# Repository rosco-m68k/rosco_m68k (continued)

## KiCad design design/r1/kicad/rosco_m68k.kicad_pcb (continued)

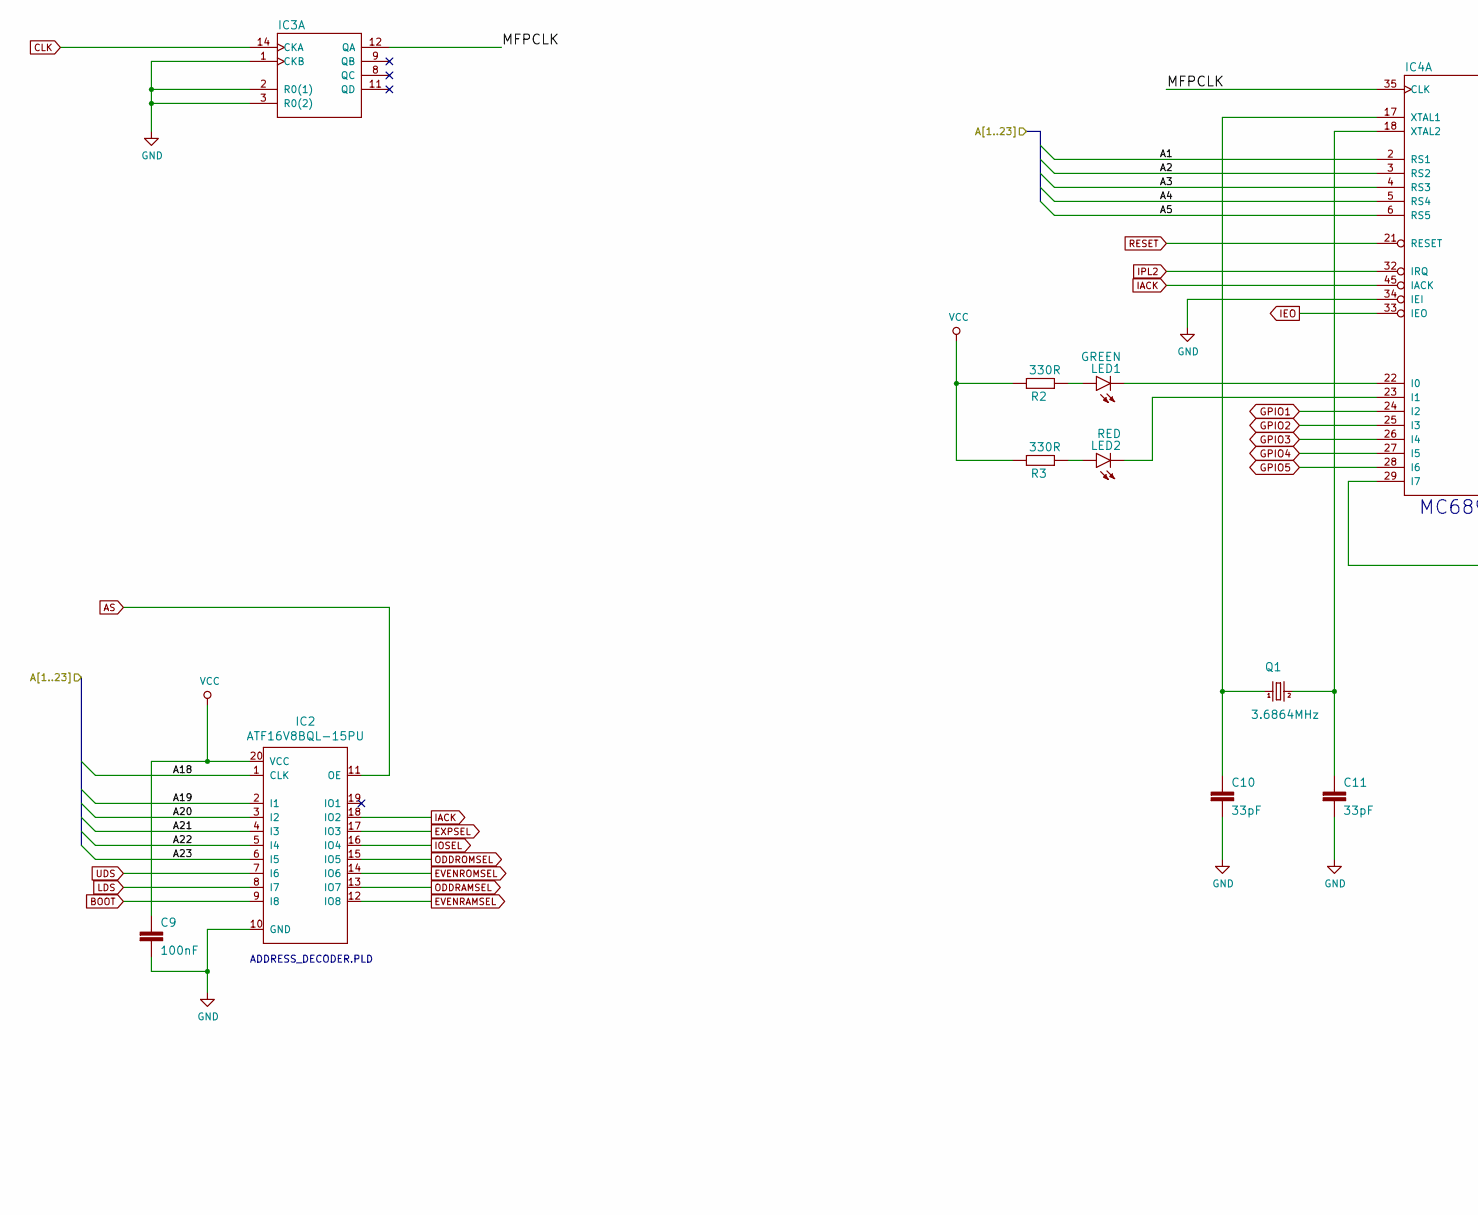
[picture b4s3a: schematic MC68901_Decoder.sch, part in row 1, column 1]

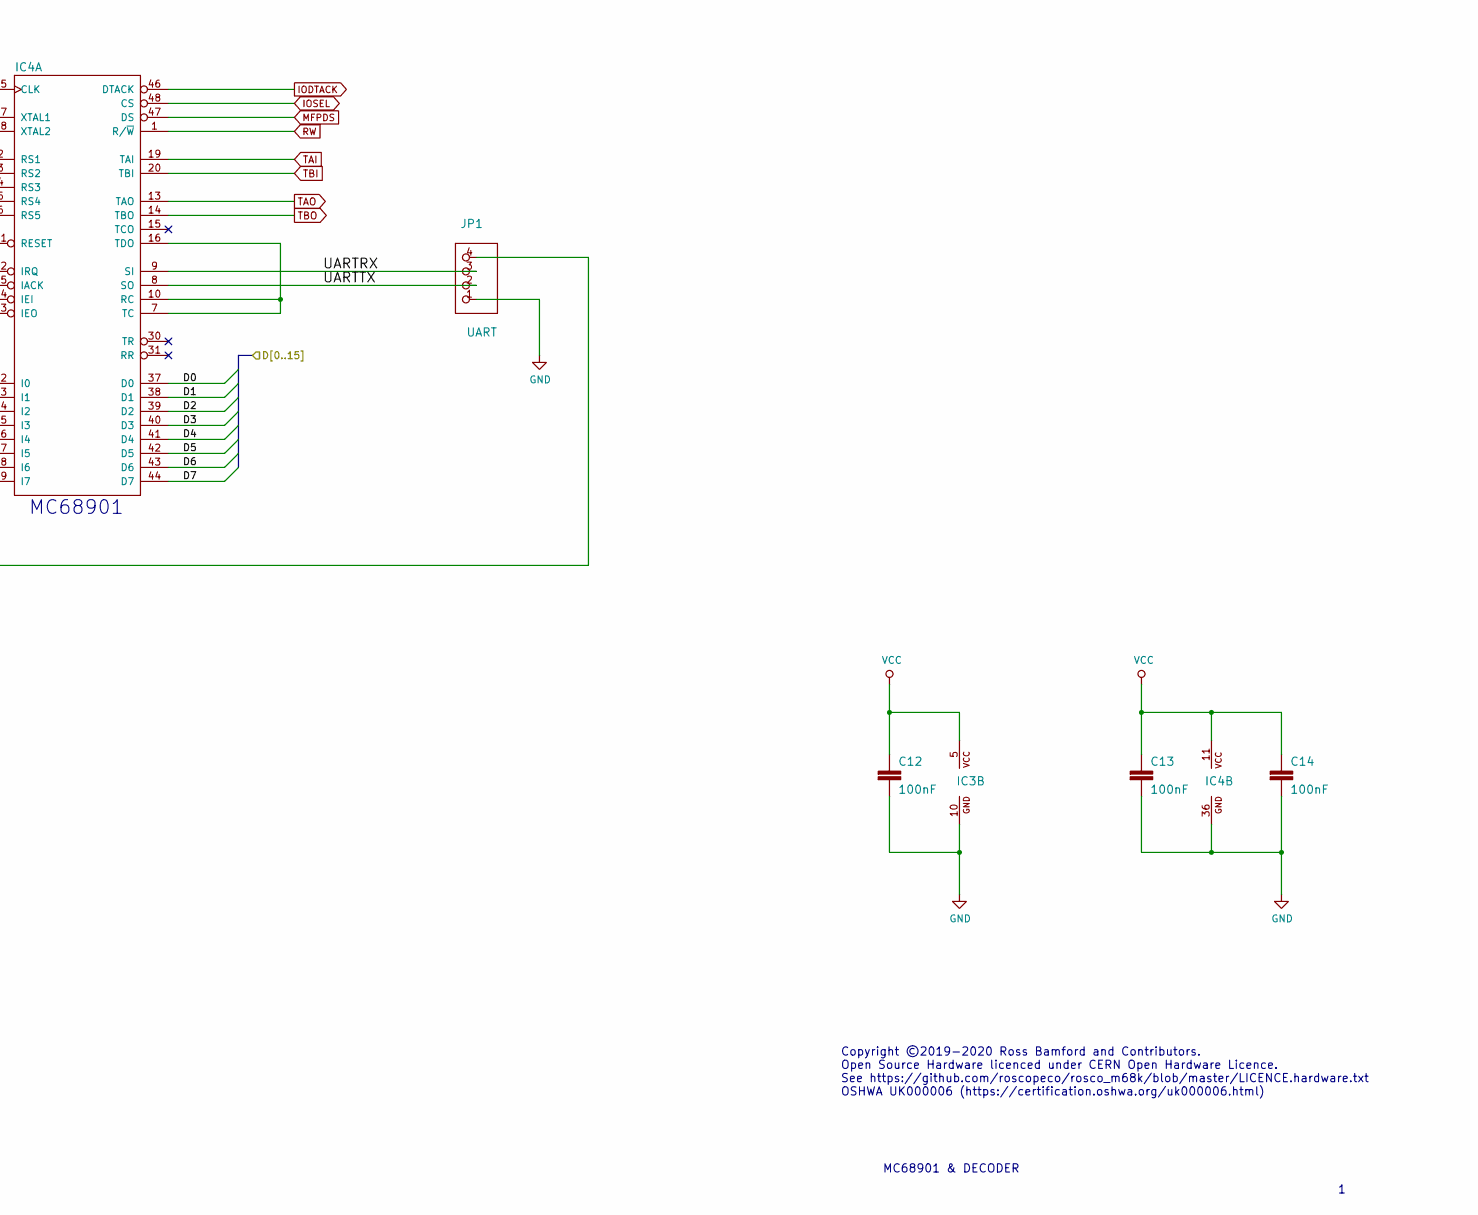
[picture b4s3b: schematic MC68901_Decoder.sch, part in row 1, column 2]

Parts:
C9, C12, C13, C14: 100nF; C2.5-3
C10, C11: 33pF; C2.5-3
IC2: ATF16V8BQL-15PU
IC3: 7493N; DIL14
IC4: MC68901P; DIL48
JP1: UART; 1X04
LED1: GREEN; LED5MM
LED2: RED; LED5MM
Q1: 3.6864MHz; HC49_S
R2, R3: 330R; 0207_10

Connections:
/Cpu_Ram_Rom/A1: IC4.2 (RS1); also elsewhere on the board
/Cpu_Ram_Rom/A2: IC4.3 (RS2); also elsewhere on the board
/Cpu_Ram_Rom/A3: IC4.4 (RS3); also elsewhere on the board
/Cpu_Ram_Rom/A4: IC4.5 (RS4); also elsewhere on the board
/Cpu_Ram_Rom/A5: IC4.6 (RS5); also elsewhere on the board
/Cpu_Ram_Rom/A18: IC2.1 (CLK); also elsewhere on the board
/Cpu_Ram_Rom/A19: IC2.2 (I1); also elsewhere on the board
/Cpu_Ram_Rom/A20: IC2.3 (I2); also elsewhere on the board
/Cpu_Ram_Rom/A21: IC2.4 (I3); also elsewhere on the board
/Cpu_Ram_Rom/A22: IC2.5 (I4); also elsewhere on the board
/Cpu_Ram_Rom/A23: IC2.6 (I5); also elsewhere on the board
/Cpu_Ram_Rom/D0: IC4.37 (D0); also elsewhere on the board
/Cpu_Ram_Rom/D1: IC4.38 (D1); also elsewhere on the board
/Cpu_Ram_Rom/D2: IC4.39 (D2); also elsewhere on the board
/Cpu_Ram_Rom/D3: IC4.40 (D3); also elsewhere on the board
/Cpu_Ram_Rom/D4: IC4.41 (D4); also elsewhere on the board
/Cpu_Ram_Rom/D5: IC4.42 (D5); also elsewhere on the board
/Cpu_Ram_Rom/D6: IC4.43 (D6); also elsewhere on the board
/Cpu_Ram_Rom/D7: IC4.44 (D7); also elsewhere on the board
/MC68901_Decoder/MFPCLK: IC3.12 (QA), IC4.35 (CLK)
/MC68901_Decoder/UARTRX: IC4.9 (SI), JP1.3
/MC68901_Decoder/UARTTX: IC4.8 (SO), JP1.2
AS: IC2.11 (OE); also elsewhere on the board
BOOT: IC2.9 (I8); also elsewhere on the board
CLK: IC3.14 (CKA); also elsewhere on the board
EVENRAMSEL: IC2.12 (IO8); also elsewhere on the board
EVENROMSEL: IC2.14 (IO6); also elsewhere on the board
EXPSEL: IC2.17 (IO3); also elsewhere on the board
GND: C9.2, C10.2, C11.2, C12.2, C13.2, C14.2, IC2.10 (GND), IC3.1 (CKB), IC3.2 (R0(1)), IC3.3 (R0(2)), IC3.10 (GND), IC4.34 (IEI), IC4.36 (GND), JP1.1; also elsewhere on the board
GPIO1: IC4.24 (I2); also elsewhere on the board
GPIO2: IC4.25 (I3); also elsewhere on the board
GPIO3: IC4.26 (I4); also elsewhere on the board
GPIO4: IC4.27 (I5); also elsewhere on the board
GPIO5: IC4.28 (I6); also elsewhere on the board
IACK: IC2.18 (IO2), IC4.45 (IACK); also elsewhere on the board
IEO: IC4.33 (IEO); also elsewhere on the board
IODTACK: IC4.46 (DTACK); also elsewhere on the board
IOSEL: IC2.16 (IO4), IC4.48 (CS); also elsewhere on the board
IPL2: IC4.32 (IRQ); also elsewhere on the board
LDS: IC2.8 (I7); also elsewhere on the board
MFPDS: IC4.47 (DS); also elsewhere on the board
unnamed: C10.1, IC4.17 (XTAL1), Q1.1
unnamed: C11.1, IC4.18 (XTAL2), Q1.2
unnamed: IC4.7 (TC), IC4.10 (RC), IC4.16 (TDO)
unnamed: IC4.22 (I0), LED1.K (C)
unnamed: IC4.23 (I1), LED2.K (C)
unnamed: IC4.29 (I7), JP1.4
unnamed: LED1.A, R2.1
unnamed: LED2.A, R3.1
ODDRAMSEL: IC2.13 (IO7); also elsewhere on the board
ODDROMSEL: IC2.15 (IO5); also elsewhere on the board
RESET: IC4.21 (RESET); also elsewhere on the board
RW: IC4.1 (R/~W); also elsewhere on the board
TAI: IC4.19 (TAI); also elsewhere on the board
TAO: IC4.13 (TAO); also elsewhere on the board
TBI: IC4.20 (TBI); also elsewhere on the board
TBO: IC4.14 (TBO); also elsewhere on the board
UDS: IC2.7 (I6); also elsewhere on the board
VCC: C9.1, C12.1, C13.1, C14.1, IC2.20 (VCC), IC3.5 (VCC), IC4.11 (VCC), R2.2, R3.2; also elsewhere on the board

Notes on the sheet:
Copyright ©2019-2020 Ross Bamford and Contributors. Open Source Hardware licenced under CERN Open Hardware Licence. See https://github.com/roscopeco/rosco_m68k/blob/master/LICENCE.hardware.txt OSHWA UK000006 (https://certification.oshwa.org/uk000006.html)
MC68901 & DECODER
MC68901
ADDRESS_DECODER.PLD

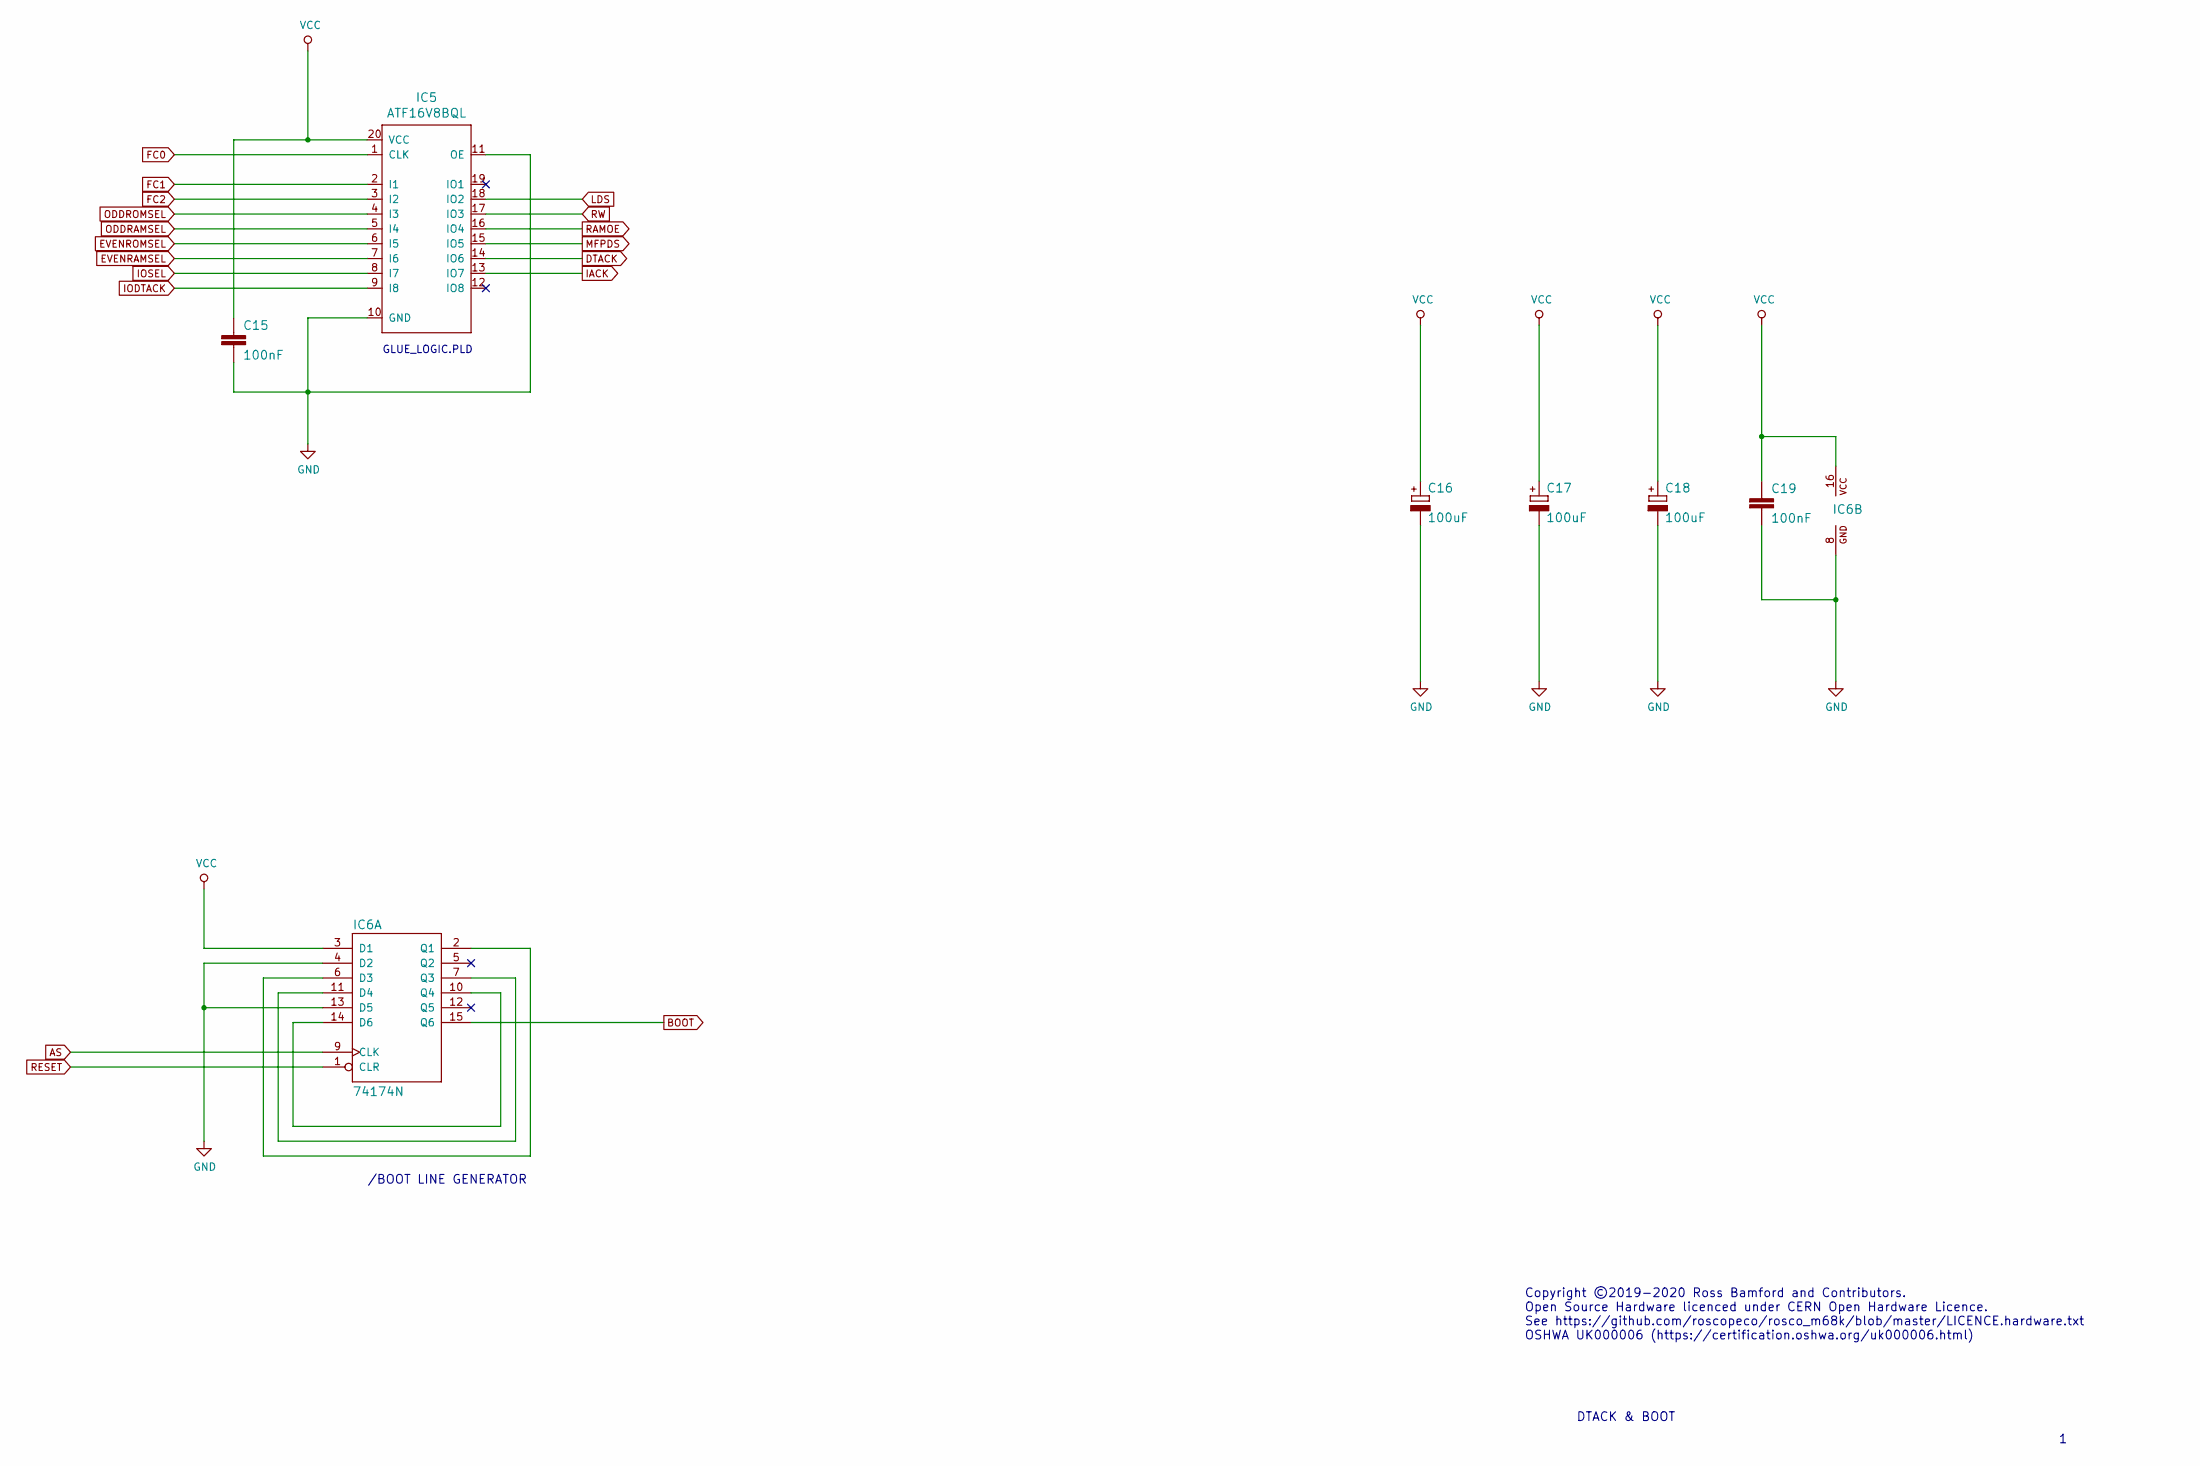
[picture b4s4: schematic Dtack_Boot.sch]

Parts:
C15, C19: 100nF; C2.5-3
C16, C17, C18: 100uF; E2,5-5
IC5: ATF16V8BQL
IC6: 74174N; DIL16

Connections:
AS: IC6.9 (CLK); also elsewhere on the board
BOOT: IC6.15 (Q6); also elsewhere on the board
DTACK: IC5.14 (IO6); also elsewhere on the board
EVENRAMSEL: IC5.7 (I6); also elsewhere on the board
EVENROMSEL: IC5.6 (I5); also elsewhere on the board
FC0: IC5.1 (CLK); also elsewhere on the board
FC1: IC5.2 (I1); also elsewhere on the board
FC2: IC5.3 (I2); also elsewhere on the board
GND: C15.2, C16.-, C17.-, C18.-, C19.2, IC5.10 (GND), IC5.11 (OE), IC6.4 (D2), IC6.8 (GND), IC6.13 (D5); also elsewhere on the board
IACK: IC5.13 (IO7); also elsewhere on the board
IODTACK: IC5.9 (I8); also elsewhere on the board
IOSEL: IC5.8 (I7); also elsewhere on the board
LDS: IC5.18 (IO2); also elsewhere on the board
MFPDS: IC5.15 (IO5); also elsewhere on the board
unnamed: IC6.2 (Q1), IC6.6 (D3)
unnamed: IC6.10 (Q4), IC6.14 (D6)
unnamed: IC6.7 (Q3), IC6.11 (D4)
ODDRAMSEL: IC5.5 (I4); also elsewhere on the board
ODDROMSEL: IC5.4 (I3); also elsewhere on the board
RAMOE: IC5.16 (IO4); also elsewhere on the board
RESET: IC6.1 (CLR); also elsewhere on the board
RW: IC5.17 (IO3); also elsewhere on the board
VCC: C15.1, C16.+, C17.+, C18.+, C19.1, IC5.20 (VCC), IC6.3 (D1), IC6.16 (VCC); also elsewhere on the board

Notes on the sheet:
/BOOT LINE GENERATOR
Copyright ©2019-2020 Ross Bamford and Contributors. Open Source Hardware licenced under CERN Open Hardware Licence. See https://github.com/roscopeco/rosco_m68k/blob/master/LICENCE.hardware.txt OSHWA UK000006 (https://certification.oshwa.org/uk000006.html)
DTACK & BOOT
GLUE_LOGIC.PLD

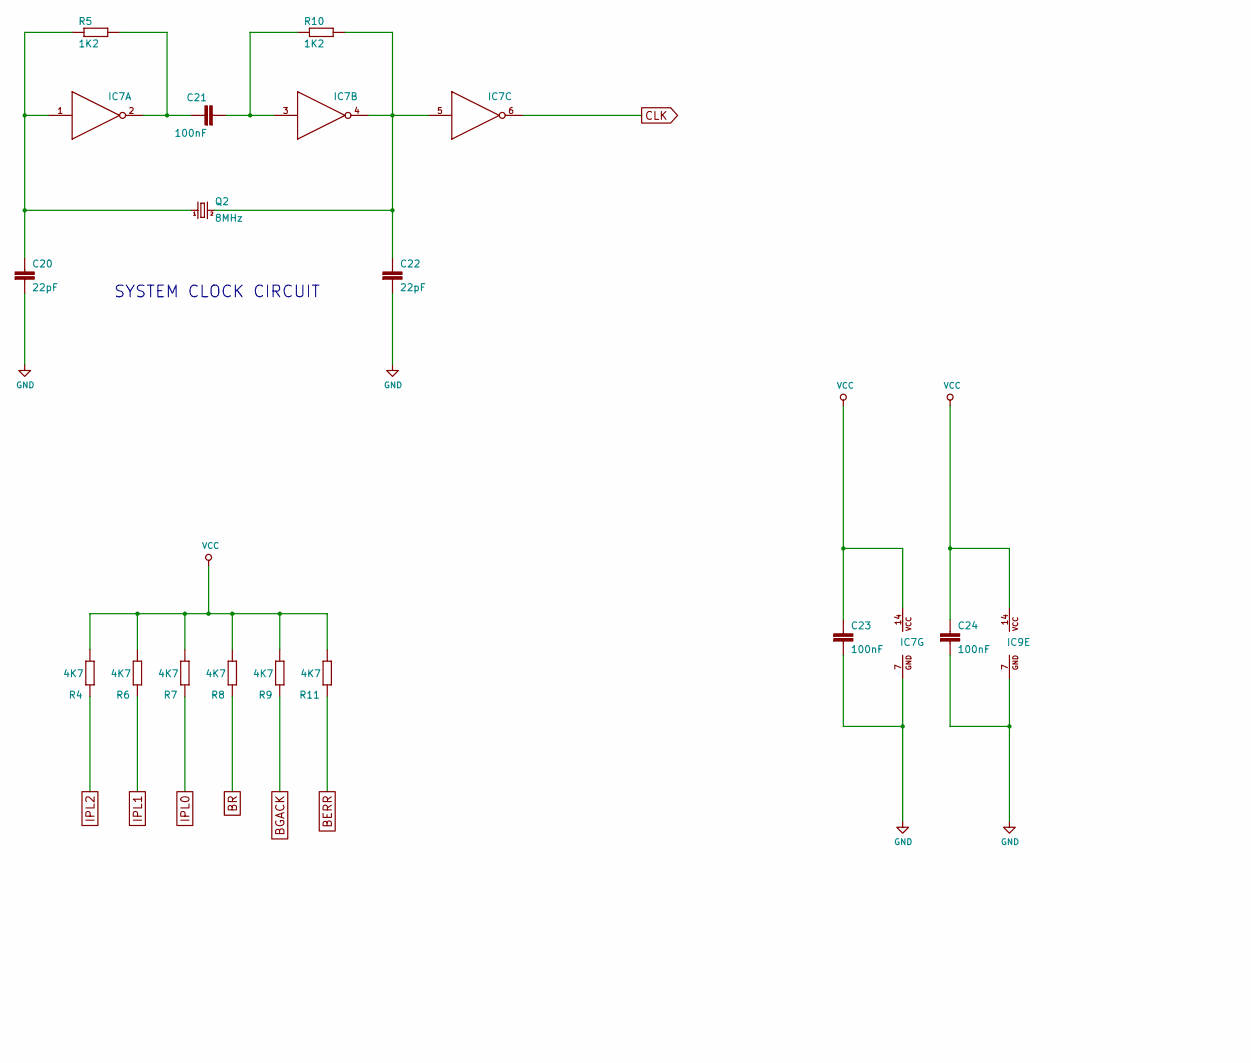
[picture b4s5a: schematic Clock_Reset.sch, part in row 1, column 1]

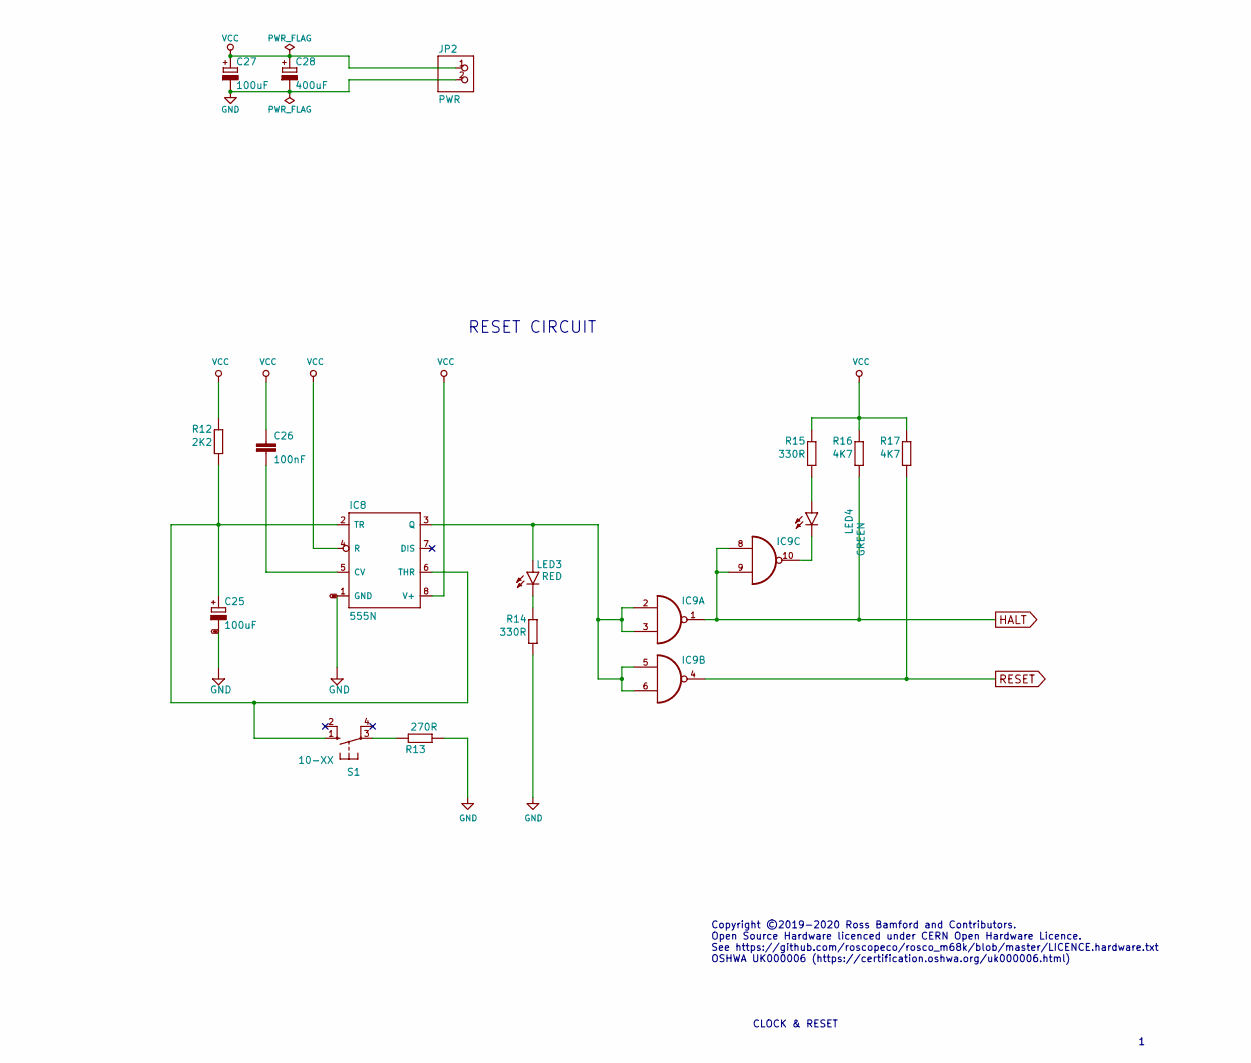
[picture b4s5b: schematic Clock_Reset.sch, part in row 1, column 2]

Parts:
C20, C22: 22pF; C2.5-3
C21, C23, C24, C26: 100nF; C2.5-3
C25, C27: 100uF; E2,5-5
C28: 400uF; E3,5-10
IC7: 7404N; DIL14
IC8: 555N; DIL08
IC9: 74LS01N; DIL14
JP2: PWR; 1X02
LED3: RED; LED5MM
LED4: GREEN; LED5MM
Q2: 8MHz; HC49_S
R4, R6, R7, R8, R9, R11, R16, R17: 4K7; 0207_10
R5, R10: 1K2; 0207_10
R12: 2K2; 0207_10
R13: 270R; 0207_10
R14, R15: 330R; 0207_10
S1: 10-XX; B3F-10XX

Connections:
BERR: R11.1; also elsewhere on the board
BGACK: R9.1; also elsewhere on the board
BR: R8.1; also elsewhere on the board
CLK: IC7.6 (O); also elsewhere on the board
GND: C20.2, C22.2, C23.2, C24.2, C25.-, C27.-, C28.-, IC7.7 (GND), IC8.1 (GND), IC9.7 (GND), JP2.2, R13.1, R14.1; also elsewhere on the board
HALT: IC9.1 (O), IC9.8 (I0), IC9.9 (I1), R16.1; also elsewhere on the board
IPL0: R7.1; also elsewhere on the board
IPL1: R6.1; also elsewhere on the board
IPL2: R4.1; also elsewhere on the board
unnamed: C20.1, IC7.1 (I), Q2.1, R5.1
unnamed: C21.1, IC7.2 (O), R5.2
unnamed: C21.2, IC7.3 (I), R10.1
unnamed: C22.1, IC7.4 (O), IC7.5 (I), Q2.2, R10.2
unnamed: C25.+, IC8.2 (TR), IC8.6 (THR), R12.1, S1.1 (S)
unnamed: C26.2, IC8.5 (CV)
unnamed: IC8.3 (Q), IC9.2 (I0), IC9.3 (I1), IC9.5 (I0), IC9.6 (I1), LED3.A
unnamed: IC9.10 (O), LED4.K (C)
unnamed: LED3.K (C), R14.2
unnamed: LED4.A, R15.1
unnamed: R13.2, S1.3
RESET: IC9.4 (O), R17.1; also elsewhere on the board
VCC: C23.1, C24.1, C26.1, C27.+, C28.+, IC7.14 (VCC), IC8.4 (R), IC8.8 (V+), IC9.14 (VCC), JP2.1, R4.2, R6.2, R7.2, R8.2, R9.2, R11.2, R12.2, R15.2, R16.2, R17.2; also elsewhere on the board

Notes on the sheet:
RESET CIRCUIT
SYSTEM CLOCK CIRCUIT
CLOCK & RESET
Copyright ©2019-2020 Ross Bamford and Contributors. Open Source Hardware licenced under CERN Open Hardware Licence. See https://github.com/roscopeco/rosco_m68k/blob/master/LICENCE.hardware.txt OSHWA UK000006 (https://certification.oshwa.org/uk000006.html)

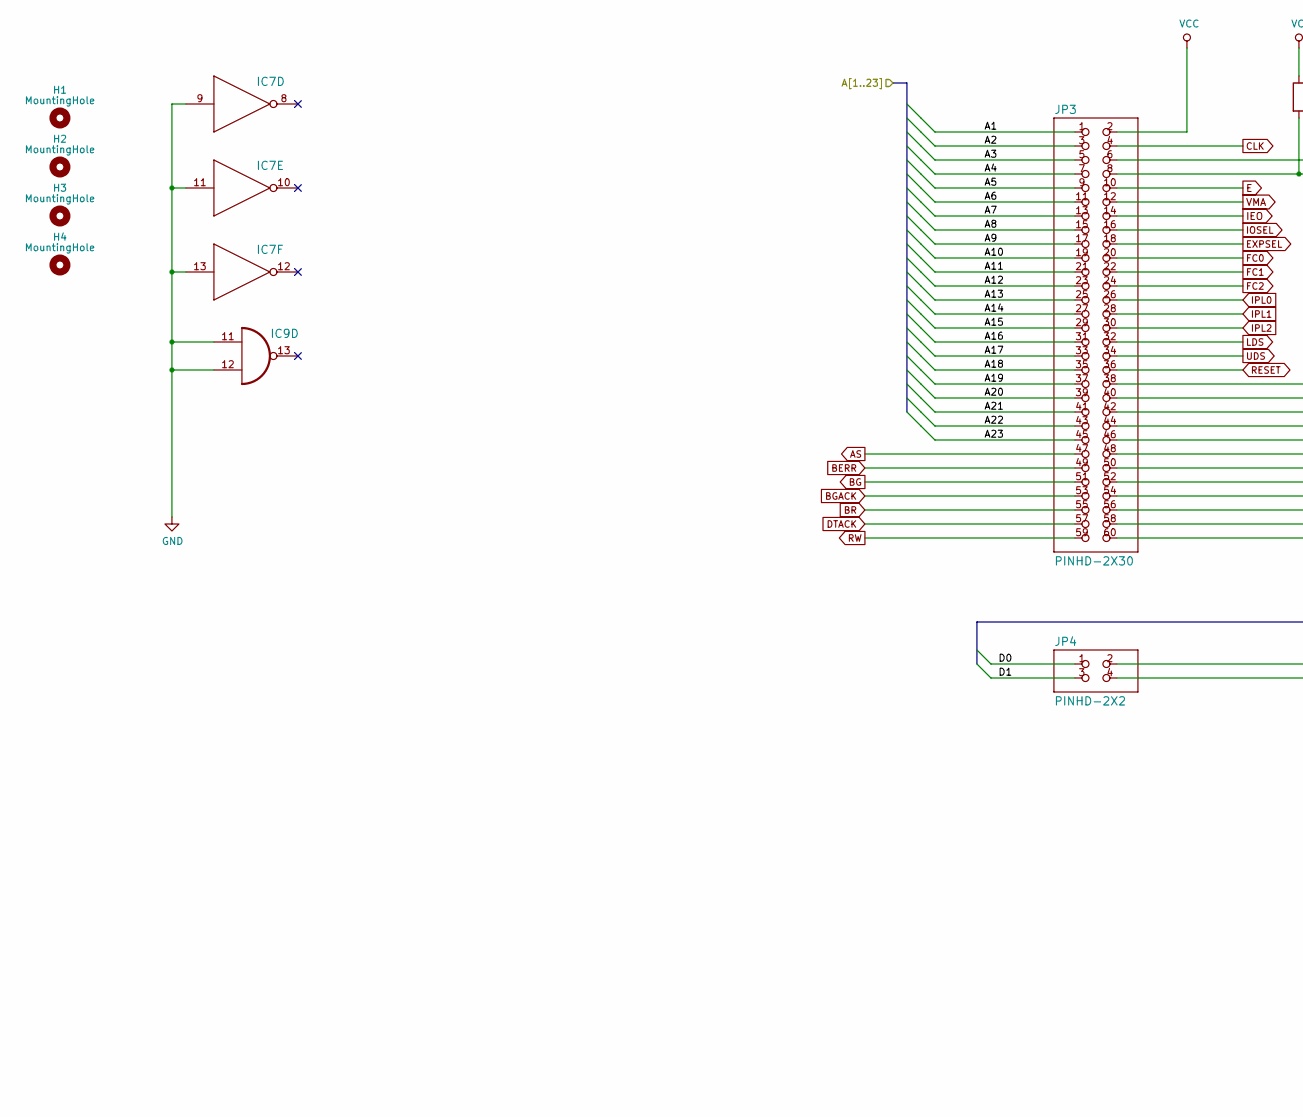
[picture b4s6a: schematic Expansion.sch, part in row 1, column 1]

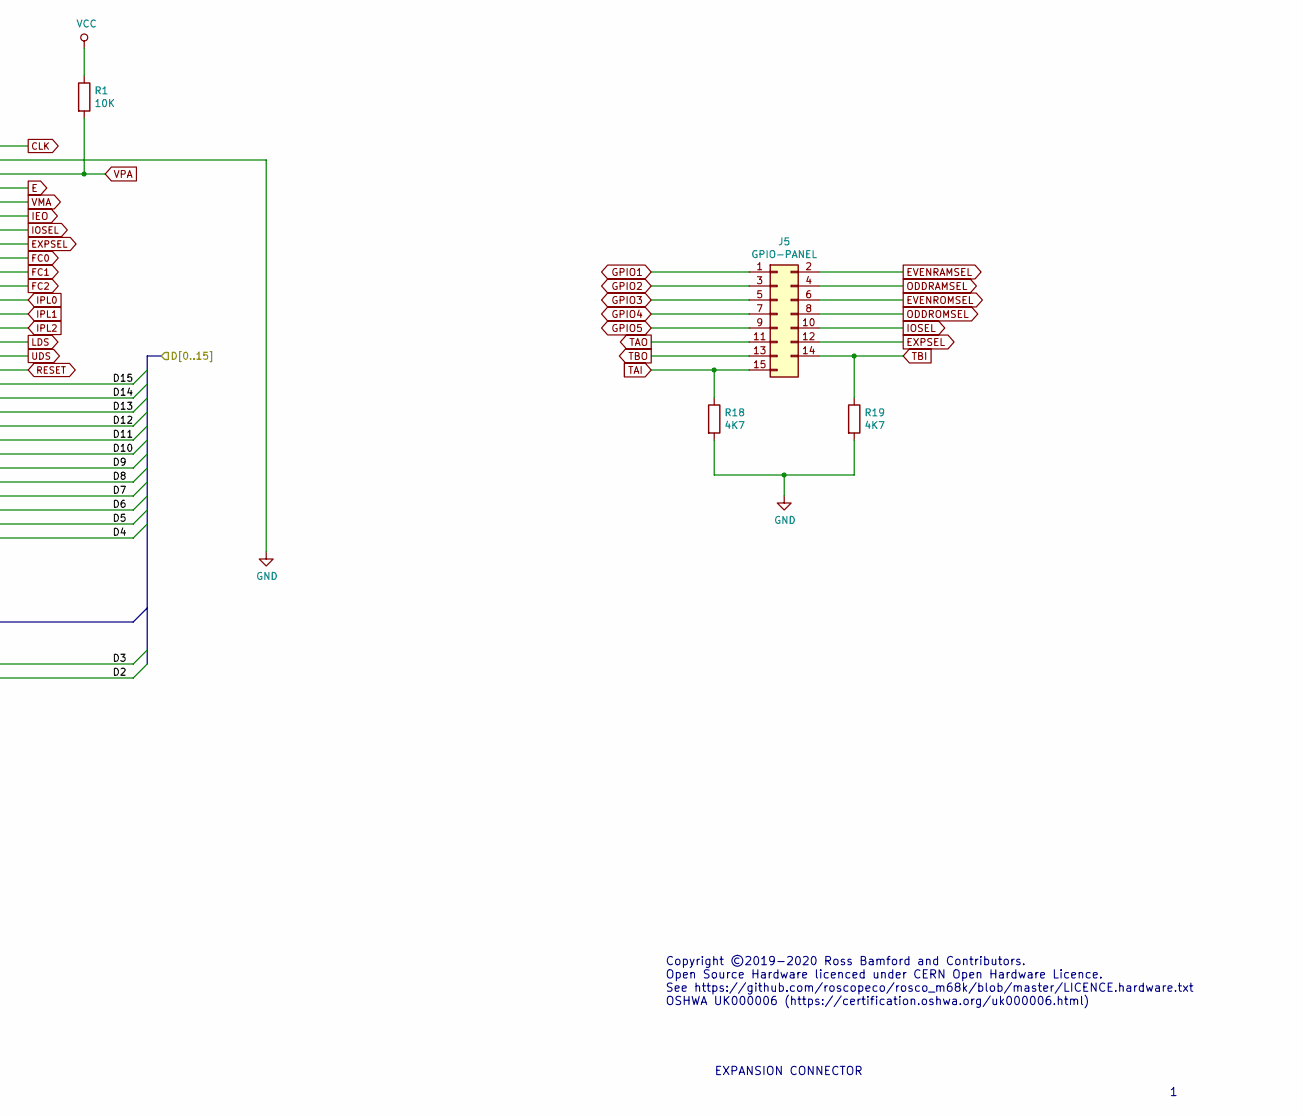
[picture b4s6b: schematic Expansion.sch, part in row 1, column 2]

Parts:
H1, H2, H3, H4: MountingHole; MountingHole_3.2mm_M3
IC7: 7404N; DIL14
IC9: 74LS01N; DIL14
J5: GPIO-PANEL; PinHeader_2x08_P2.54mm_Vertical
JP3: PINHD-2X30; 2X30
JP4: PINHD-2X2; 2X02
R1: 10K; 0207_10
R18, R19: 4K7; 0207_10

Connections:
/Cpu_Ram_Rom/A1: JP3.1; also elsewhere on the board
/Cpu_Ram_Rom/A2: JP3.3; also elsewhere on the board
/Cpu_Ram_Rom/A3: JP3.5; also elsewhere on the board
/Cpu_Ram_Rom/A4: JP3.7; also elsewhere on the board
/Cpu_Ram_Rom/A5: JP3.9; also elsewhere on the board
/Cpu_Ram_Rom/A6: JP3.11; also elsewhere on the board
/Cpu_Ram_Rom/A7: JP3.13; also elsewhere on the board
/Cpu_Ram_Rom/A8: JP3.15; also elsewhere on the board
/Cpu_Ram_Rom/A9: JP3.17; also elsewhere on the board
/Cpu_Ram_Rom/A10: JP3.19; also elsewhere on the board
/Cpu_Ram_Rom/A11: JP3.21; also elsewhere on the board
/Cpu_Ram_Rom/A12: JP3.23; also elsewhere on the board
/Cpu_Ram_Rom/A13: JP3.25; also elsewhere on the board
/Cpu_Ram_Rom/A14: JP3.27; also elsewhere on the board
/Cpu_Ram_Rom/A15: JP3.29; also elsewhere on the board
/Cpu_Ram_Rom/A16: JP3.31; also elsewhere on the board
/Cpu_Ram_Rom/A17: JP3.33; also elsewhere on the board
/Cpu_Ram_Rom/A18: JP3.35; also elsewhere on the board
/Cpu_Ram_Rom/A19: JP3.37; also elsewhere on the board
/Cpu_Ram_Rom/A20: JP3.39; also elsewhere on the board
/Cpu_Ram_Rom/A21: JP3.41; also elsewhere on the board
/Cpu_Ram_Rom/A22: JP3.43; also elsewhere on the board
/Cpu_Ram_Rom/A23: JP3.45; also elsewhere on the board
/Cpu_Ram_Rom/D0: JP4.1; also elsewhere on the board
/Cpu_Ram_Rom/D1: JP4.3; also elsewhere on the board
/Cpu_Ram_Rom/D2: JP4.4; also elsewhere on the board
/Cpu_Ram_Rom/D3: JP4.2; also elsewhere on the board
/Cpu_Ram_Rom/D4: JP3.60; also elsewhere on the board
/Cpu_Ram_Rom/D5: JP3.58; also elsewhere on the board
/Cpu_Ram_Rom/D6: JP3.56; also elsewhere on the board
/Cpu_Ram_Rom/D7: JP3.54; also elsewhere on the board
/Cpu_Ram_Rom/D8: JP3.52; also elsewhere on the board
/Cpu_Ram_Rom/D9: JP3.50; also elsewhere on the board
/Cpu_Ram_Rom/D10: JP3.48; also elsewhere on the board
/Cpu_Ram_Rom/D11: JP3.46; also elsewhere on the board
/Cpu_Ram_Rom/D12: JP3.44; also elsewhere on the board
/Cpu_Ram_Rom/D13: JP3.42; also elsewhere on the board
/Cpu_Ram_Rom/D14: JP3.40; also elsewhere on the board
/Cpu_Ram_Rom/D15: JP3.38; also elsewhere on the board
AS: JP3.47; also elsewhere on the board
BERR: JP3.49; also elsewhere on the board
BG: JP3.51; also elsewhere on the board
BGACK: JP3.53; also elsewhere on the board
BR: JP3.55; also elsewhere on the board
CLK: JP3.4; also elsewhere on the board
DTACK: JP3.57; also elsewhere on the board
E: JP3.10; also elsewhere on the board
EVENRAMSEL: J5.2; also elsewhere on the board
EVENROMSEL: J5.6; also elsewhere on the board
EXPSEL: J5.12, JP3.18; also elsewhere on the board
FC0: JP3.20; also elsewhere on the board
FC1: JP3.22; also elsewhere on the board
FC2: JP3.24; also elsewhere on the board
GND: IC7.9 (I), IC7.11 (I), IC7.13 (I), IC9.11 (I0), IC9.12 (I1), JP3.6, R18.2, R19.2; also elsewhere on the board
GPIO1: J5.1; also elsewhere on the board
GPIO2: J5.3; also elsewhere on the board
GPIO3: J5.5; also elsewhere on the board
GPIO4: J5.7; also elsewhere on the board
GPIO5: J5.9; also elsewhere on the board
IEO: JP3.14; also elsewhere on the board
IOSEL: J5.10, JP3.16; also elsewhere on the board
IPL0: JP3.26; also elsewhere on the board
IPL1: JP3.28; also elsewhere on the board
IPL2: JP3.30; also elsewhere on the board
LDS: JP3.32; also elsewhere on the board
ODDRAMSEL: J5.4; also elsewhere on the board
ODDROMSEL: J5.8; also elsewhere on the board
RESET: JP3.36; also elsewhere on the board
RW: JP3.59; also elsewhere on the board
TAI: J5.15, R18.1; also elsewhere on the board
TAO: J5.11; also elsewhere on the board
TBI: J5.14, R19.1; also elsewhere on the board
TBO: J5.13; also elsewhere on the board
UDS: JP3.34; also elsewhere on the board
VCC: JP3.2, R1.1; also elsewhere on the board
VMA: JP3.12; also elsewhere on the board
VPA: JP3.8, R1.2; also elsewhere on the board

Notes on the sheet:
Copyright ©2019-2020 Ross Bamford and Contributors. Open Source Hardware licenced under CERN Open Hardware Licence. See https://github.com/roscopeco/rosco_m68k/blob/master/LICENCE.hardware.txt OSHWA UK000006 (https://certification.oshwa.org/uk000006.html)
EXPANSION CONNECTOR

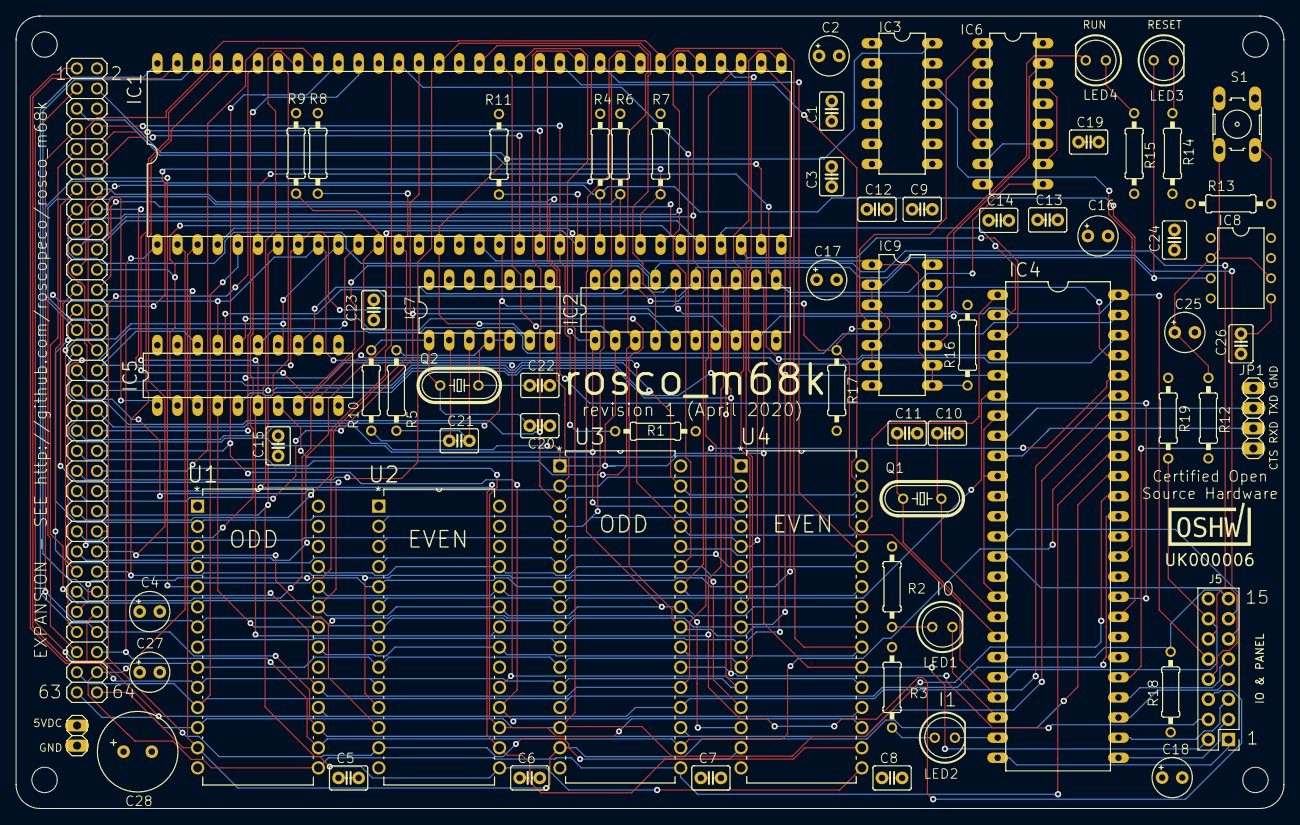
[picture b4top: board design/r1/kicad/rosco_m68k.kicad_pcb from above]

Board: 4 copper layers, 160.0 x 100.0 mm, 77 parts (0 on the bottom side), 108 nets.

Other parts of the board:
OSHW_Mono_0.25_Scale: UK000006; OSHW_Mono_0.25_Scale

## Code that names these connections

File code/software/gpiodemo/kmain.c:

/*
 *------------------------------------------------------------
 *                                  ___ ___ _   
 *  ___ ___ ___ ___ ___       _____|  _| . | |_ 
 * |  _| . |_ -|  _| . |     |     | . | . | '_|
 * |_| |___|___|___|___|_____|_|_|_|___|___|_,_| 
 *                     |_____|       firmware v1                 
 * ------------------------------------------------------------
 * Copyright (c)2020 Ross Bamford
 * See top-level LICENSE.md for licence information.
 *
 * Extremely simple example of GPIO programming.
 * ------------------------------------------------------------
 */

#include <stdnoreturn.h>
#include <stdbool.h>
#include <basicio.h>
#include <gpio.h>

static void initGPIOs() {
  pinMode(GPIO1, OUTPUT);
  pinMode(GPIO2, OUTPUT);
  pinMode(GPIO3, OUTPUT);
  pinMode(GPIO4, OUTPUT);
  pinMode(GPIO5, OUTPUT);
}

static void setGPIOs(bool g1, bool g2, bool g3, bool g4, bool g5) {
  digitalWrite(GPIO1, g1);
  digitalWrite(GPIO2, g2);
  digitalWrite(GPIO3, g3);
  digitalWrite(GPIO4, g4);
  digitalWrite(GPIO5, g5);
}

noreturn void kmain() {
  print("\033[2J");
  println("GPIO Toggle Demo");

  initGPIOs();

  while (true) {
    print("💡 ");
    setGPIOs(true, false, false, false, false);
    delay(50000);

    print("💡 ");
    setGPIOs(true, true, false, false, false);
    delay(50000);

    print("💡 ");
    setGPIOs(true, true, true, false, false);
    delay(50000);

    print("💡 ");
    setGPIOs(true, true, true, true, false);
    delay(50000);

    print("💡");
    setGPIOs(true, true, true, true, true);
    delay(50000);
    
    print("\033[80D\033[K");
    setGPIOs(false, false, false, false, false);
    delay(50000);
  }
}
